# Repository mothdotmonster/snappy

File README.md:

# snappy

snappable attinyXX7 breakout board
***
## WARNING!!!
this design has not been extensively tested yet, and may not work at all. i am only releasing it because i like sharing my ideas.

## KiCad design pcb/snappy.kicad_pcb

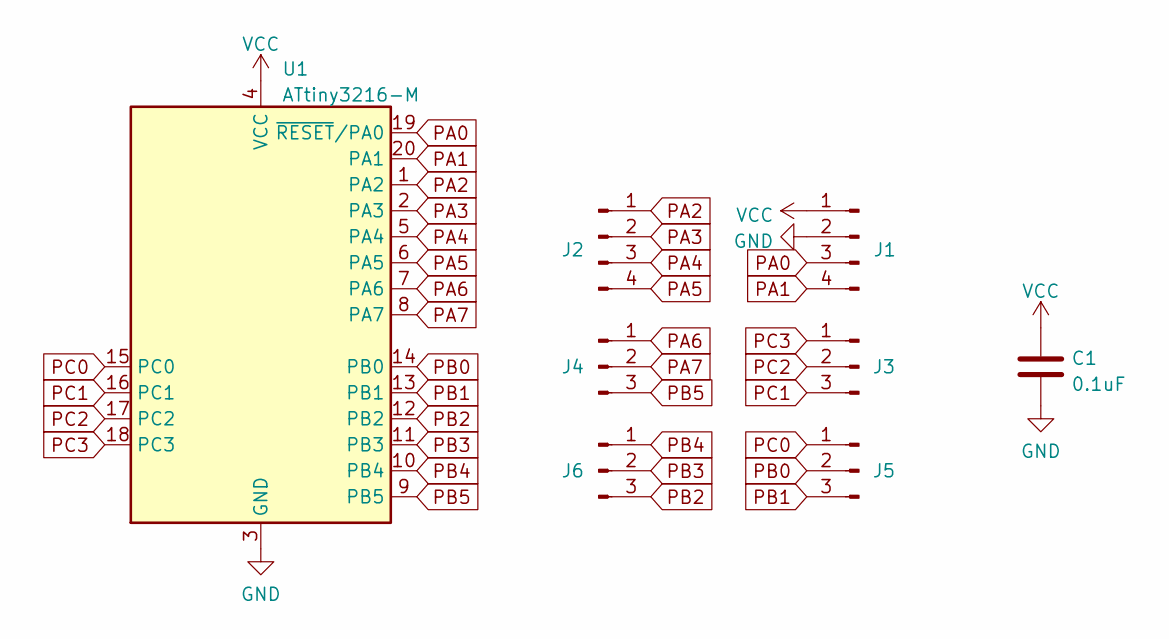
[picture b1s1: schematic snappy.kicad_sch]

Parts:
C1: 0.1uF; C_0402_1005Metric; JLC C1525
J1, J2: Conn_01x04_Male; PinHeader_1x04_P2.54mm_Vertical
J3, J4, J5, J6: Conn_01x03_Male; PinHeader_1x03_P2.54mm_Vertical
U1: ATtiny3216-M; VQFN-20-1EP_3x3mm_P0.4mm_EP1.7x1.7mm; JLC C507118

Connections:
GND: C1.2, J1.2, U1.3 (GND), U1.21 (GND)
PA0: J1.3, U1.19 (~RESET/PA0)
PA1: J1.4, U1.20 (PA1)
PA2: J2.1, U1.1 (PA2)
PA3: J2.2, U1.2 (PA3)
PA4: J2.3, U1.5 (PA4)
PA5: J2.4, U1.6 (PA5)
PA6: J4.1, U1.7 (PA6)
PA7: J4.2, U1.8 (PA7)
PB0: J5.2, U1.14 (PB0)
PB1: J5.3, U1.13 (PB1)
PB2: J6.3, U1.12 (PB2)
PB3: J6.2, U1.11 (PB3)
PB4: J6.1, U1.10 (PB4)
PB5: J4.3, U1.9 (PB5)
PC0: J5.1, U1.15 (PC0)
PC1: J3.3, U1.16 (PC1)
PC2: J3.2, U1.17 (PC2)
PC3: J3.1, U1.18 (PC3)
VCC: C1.1, J1.1, U1.4 (VCC)

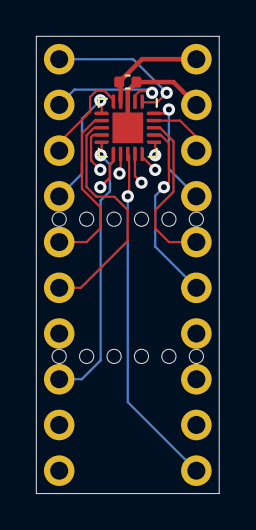
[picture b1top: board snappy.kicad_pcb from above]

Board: 4 copper layers, 10.2 x 25.4 mm, 9 parts (1 on the bottom side), 20 nets.

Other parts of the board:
kibuzzard-628A0B39: G***; kibuzzard-628A0B39
